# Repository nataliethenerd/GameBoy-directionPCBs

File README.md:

# GameBoy direction PCBs
Direction PCBs for the Game Boy line. These are common ground PCBs that can be used to create mods inside the various Game Boy Shells.

Open source, do whatever you want to do with these! But dont use it to make a submersible controller...

### Navigating this repo
Each folder includes the gerber files, and also all the KiCad files for the boards.

- *.pretty* folders contain the footprints that are used on the board.
- *.zip* files are the gerbers you send the the PCB manufacturer. Order at 1mm ENIG.

#### Game Boy DMG

| Front | Back |
|-------------| -----|
|  |  |

#### Game Boy Pocket

| Front | Back |
|-------------| -----|
|  |  |

#### Game Boy Color

| Front | Back |
|-------------| -----|
|  |  |

## Follow me

If you are into Game Boy modding or retro gaming, please consider using code "NatalieTheNerd" at:

• [Retro Modding](http://RetroModding.com) 

• [Retro Game Repair Shop](http://RetroGameRepairShop.com) 

• [Extreme Rate](http://ExtremeRate.com)

**My socials**

• [Twitter](https://twitter.com/natalie_thenerd) 

• [Instagram](https://www.instagram.com/natalie.thenerd/) 

• [Modded Gameboy Club](https://moddedgameboy.club/) - a club dedicated to the modification of Game Boys, freely sharing resources

## License

Please do not remove my logo, website and name.

The CC BY-SA 4.0 (Creative Commons Attribution-ShareAlike 4.0 International) license allows you to:

1. **Share** - Copy and redistribute the material in any medium or format.
2. **Adapt** - Remix, transform, and build upon the material for any purpose, even commercially.

### Conditions:

- **Attribution** - You must give appropriate credit, provide a link to the license, and indicate if changes were made. You may do so in any reasonable manner, but not in any way that suggests the licensor endorses you or your use.
- **ShareAlike** - If you remix, transform, or build upon the material, you must distribute your contributions under the same license as the original.

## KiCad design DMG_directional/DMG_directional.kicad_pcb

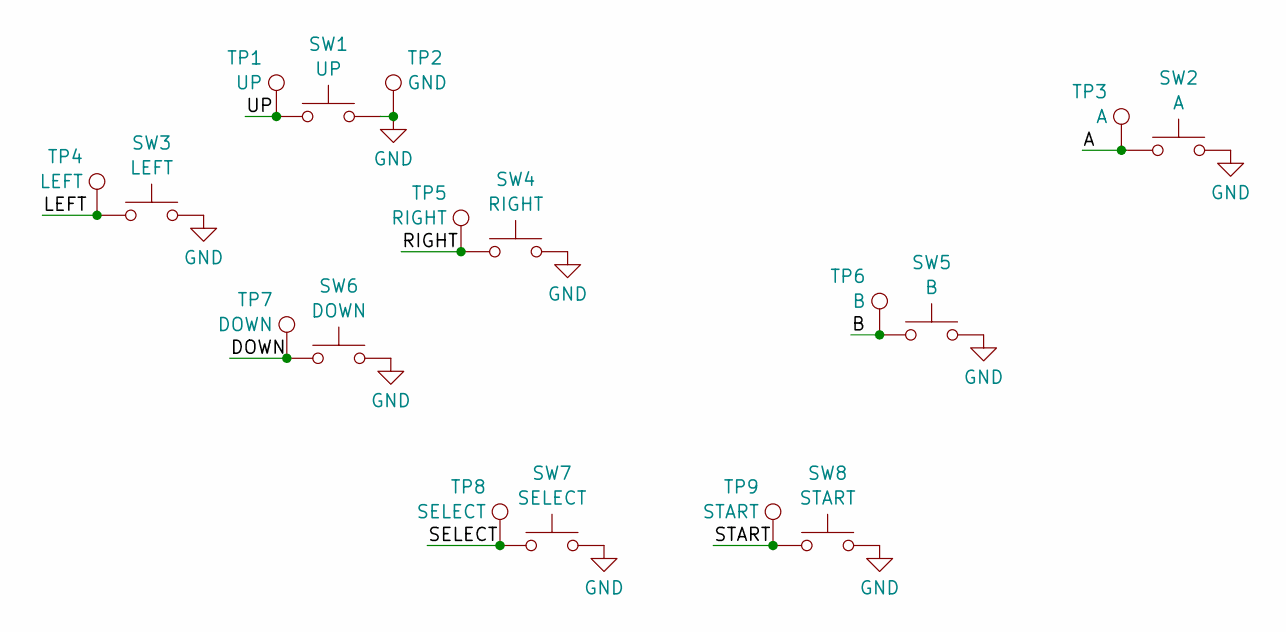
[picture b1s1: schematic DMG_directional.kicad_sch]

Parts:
SW1: UP; Dpad_DMG
SW2: A; AB_DMG
SW3: LEFT; Dpad_DMG
SW4: RIGHT; Dpad_DMG
SW5: B; AB_DMG
SW6: DOWN; Dpad_DMG
SW7: SELECT; Select_DMG
SW8: START; Start_DMG
TP1: UP; TestPoint_THTPad_D1.5mm_Drill0.7mm
TP2: GND; TestPoint_THTPad_D1.5mm_Drill0.7mm
TP3: A; TestPoint_THTPad_D1.5mm_Drill0.7mm
TP4: LEFT; TestPoint_THTPad_D1.5mm_Drill0.7mm
TP5: RIGHT; TestPoint_THTPad_D1.5mm_Drill0.7mm
TP6: B; TestPoint_THTPad_D1.5mm_Drill0.7mm
TP7: DOWN; TestPoint_THTPad_D1.5mm_Drill0.7mm
TP8: SELECT; TestPoint_THTPad_D1.5mm_Drill0.7mm
TP9: START; TestPoint_THTPad_D1.5mm_Drill0.7mm

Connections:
/A: SW2.2, TP3.1
/B: SW5.2, TP6.1
/DOWN: SW6.2, TP7.1
/LEFT: SW3.1, TP4.1
/RIGHT: SW4.2, TP5.1
/SELECT: SW7.1, TP8.1
/START: SW8.1, TP9.1
/UP: SW1.1, TP1.1
GND: SW1.2, SW2.1, SW3.2, SW4.1, SW5.1, SW6.1, SW7.2, SW8.2, TP2.1

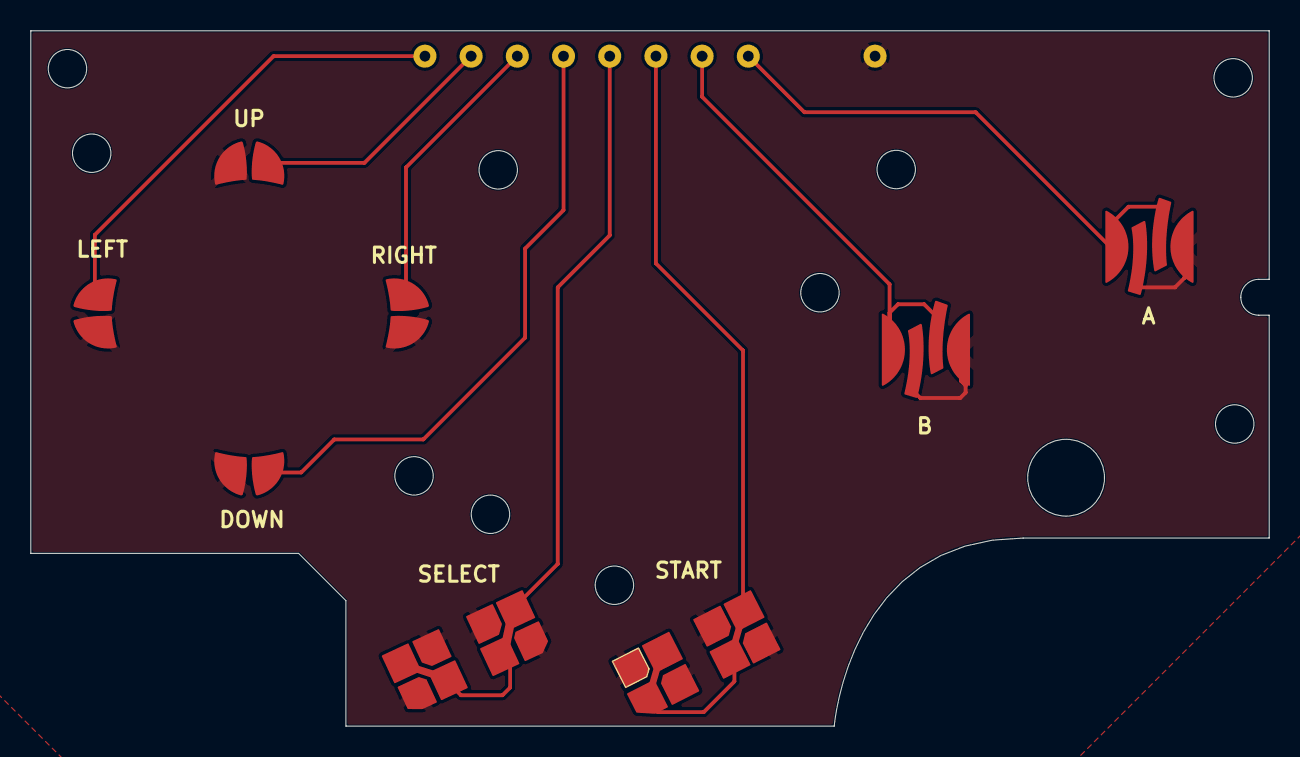
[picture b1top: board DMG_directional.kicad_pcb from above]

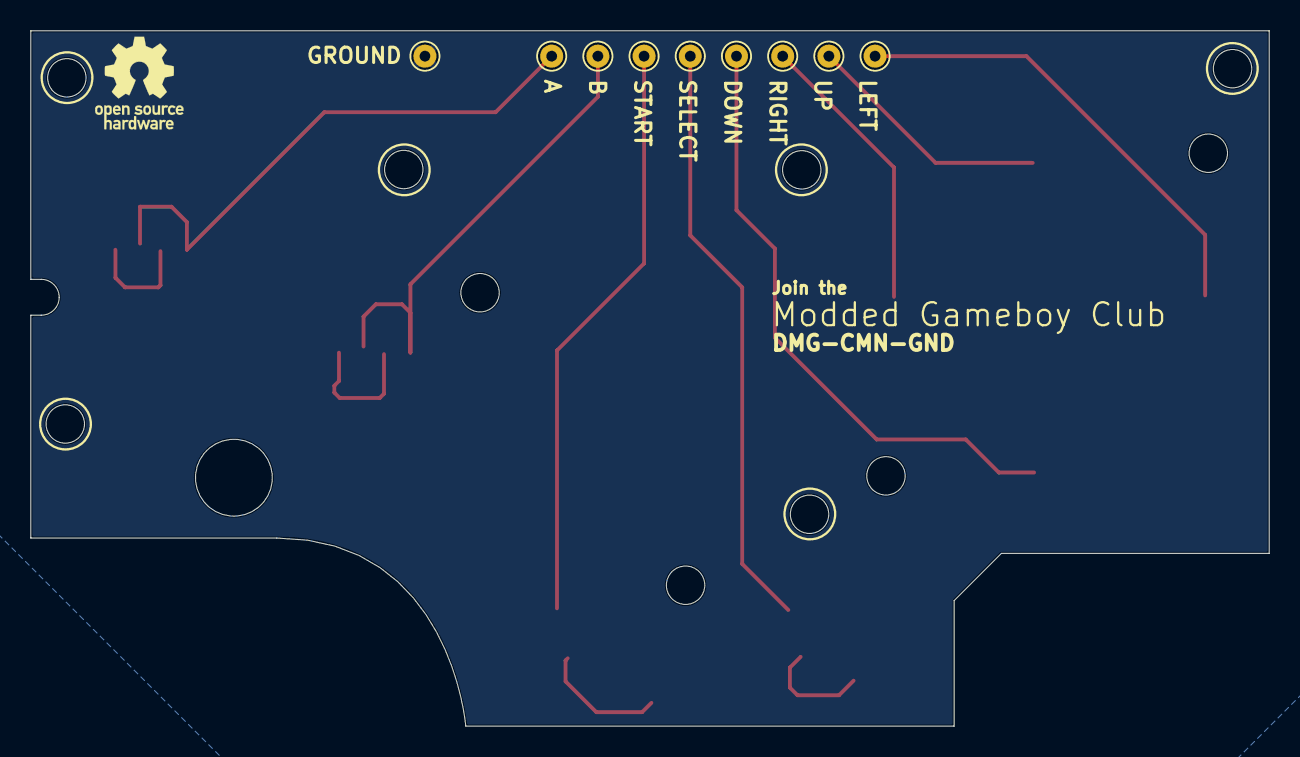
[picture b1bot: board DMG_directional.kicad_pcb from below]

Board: 2 copper layers, 80.6 x 45.3 mm, 17 parts (9 on the bottom side), 9 nets.

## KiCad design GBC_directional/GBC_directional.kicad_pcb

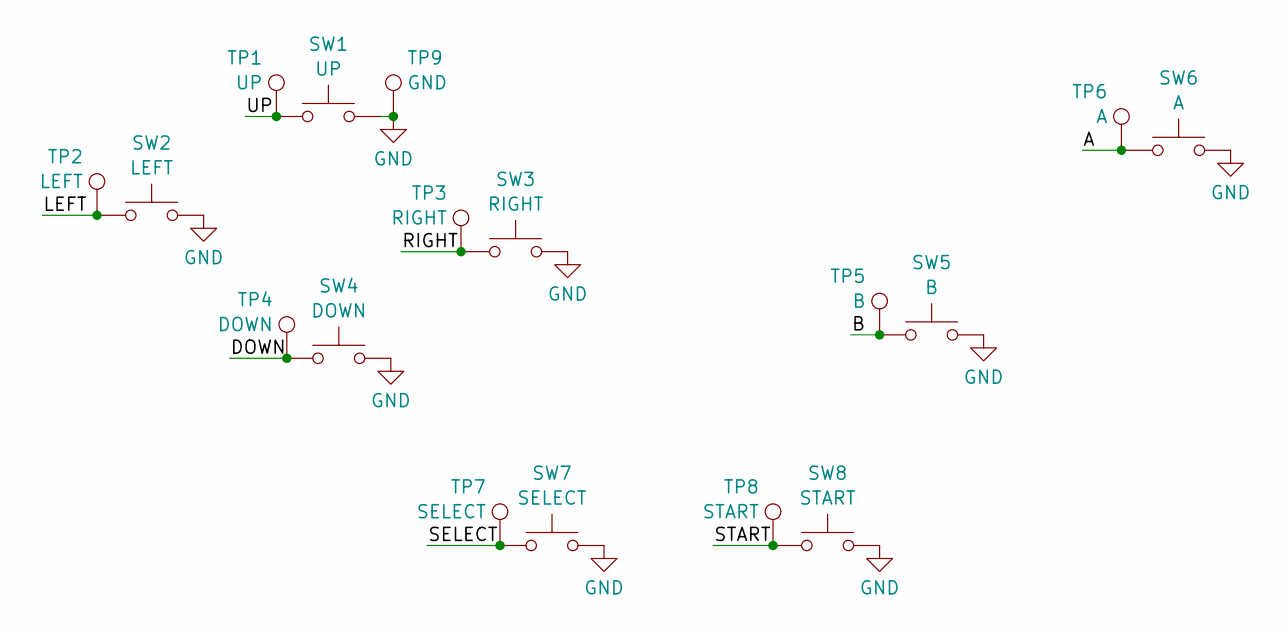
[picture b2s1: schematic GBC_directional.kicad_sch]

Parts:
SW1: UP; Dpad CGB
SW2: LEFT; Dpad CGB
SW3: RIGHT; Dpad CGB
SW4: DOWN; Dpad CGB
SW5: B; AB CGB
SW6: A; AB CGB
SW7: SELECT; Select CGB
SW8: START; Start CGB
TP1: UP; TestPoint_THTPad_D1.5mm_Drill0.7mm
TP2: LEFT; TestPoint_THTPad_D1.5mm_Drill0.7mm
TP3: RIGHT; TestPoint_THTPad_D1.5mm_Drill0.7mm
TP4: DOWN; TestPoint_THTPad_D1.5mm_Drill0.7mm
TP5: B; TestPoint_THTPad_D1.5mm_Drill0.7mm
TP6: A; TestPoint_THTPad_D1.5mm_Drill0.7mm
TP7: SELECT; TestPoint_THTPad_D1.5mm_Drill0.7mm
TP8: START; TestPoint_THTPad_D1.5mm_Drill0.7mm
TP9: GND; TestPoint_THTPad_D1.5mm_Drill0.7mm

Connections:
/A: SW6.2, TP6.1
/B: SW5.2, TP5.1
/DOWN: SW4.2, TP4.1
/LEFT: SW2.1, TP2.1
/RIGHT: SW3.2, TP3.1
/SELECT: SW7.2, TP7.1
/START: SW8.2, TP8.1
/UP: SW1.1, TP1.1
GND: SW1.2, SW2.2, SW3.1, SW4.1, SW5.1, SW6.1, SW7.1, SW8.1, TP9.1

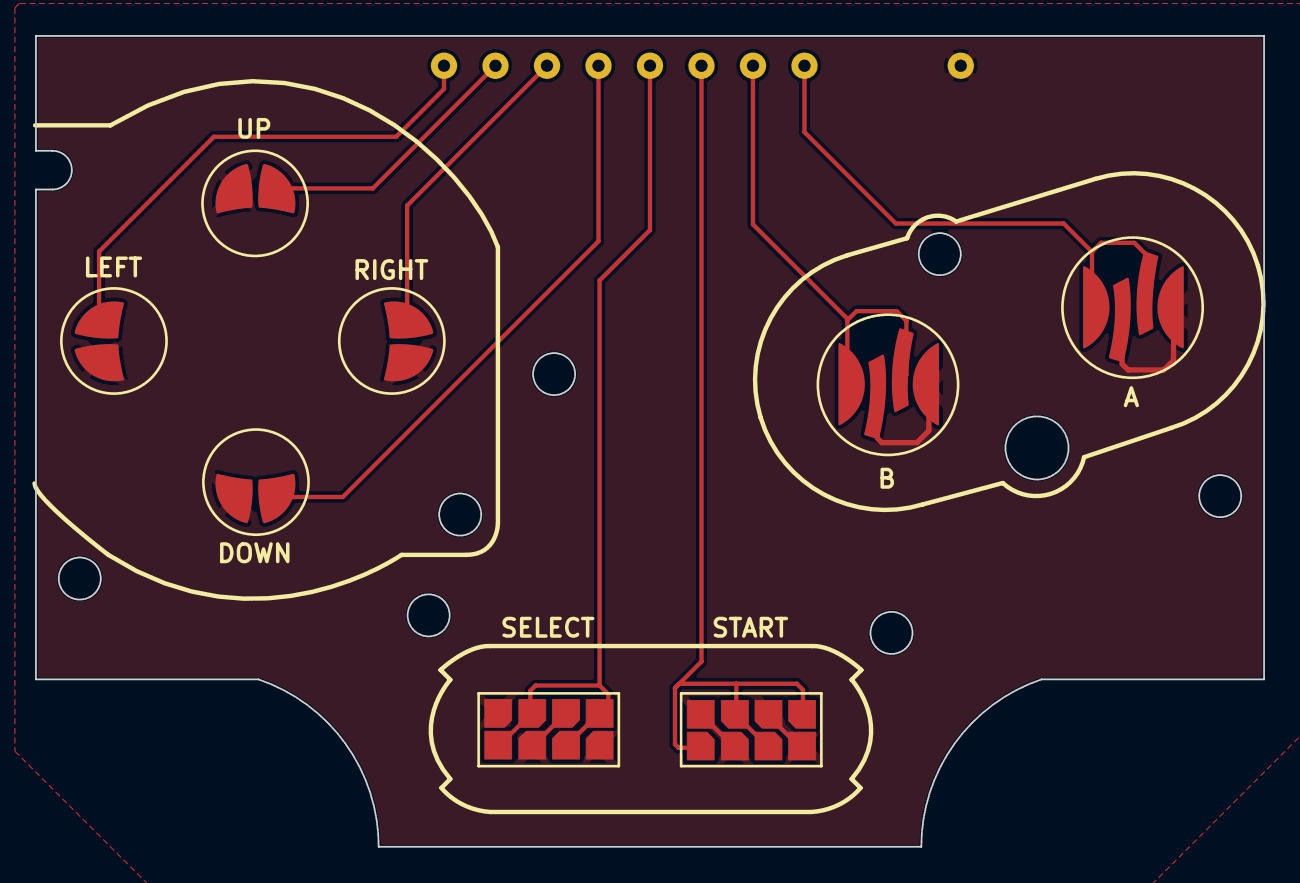
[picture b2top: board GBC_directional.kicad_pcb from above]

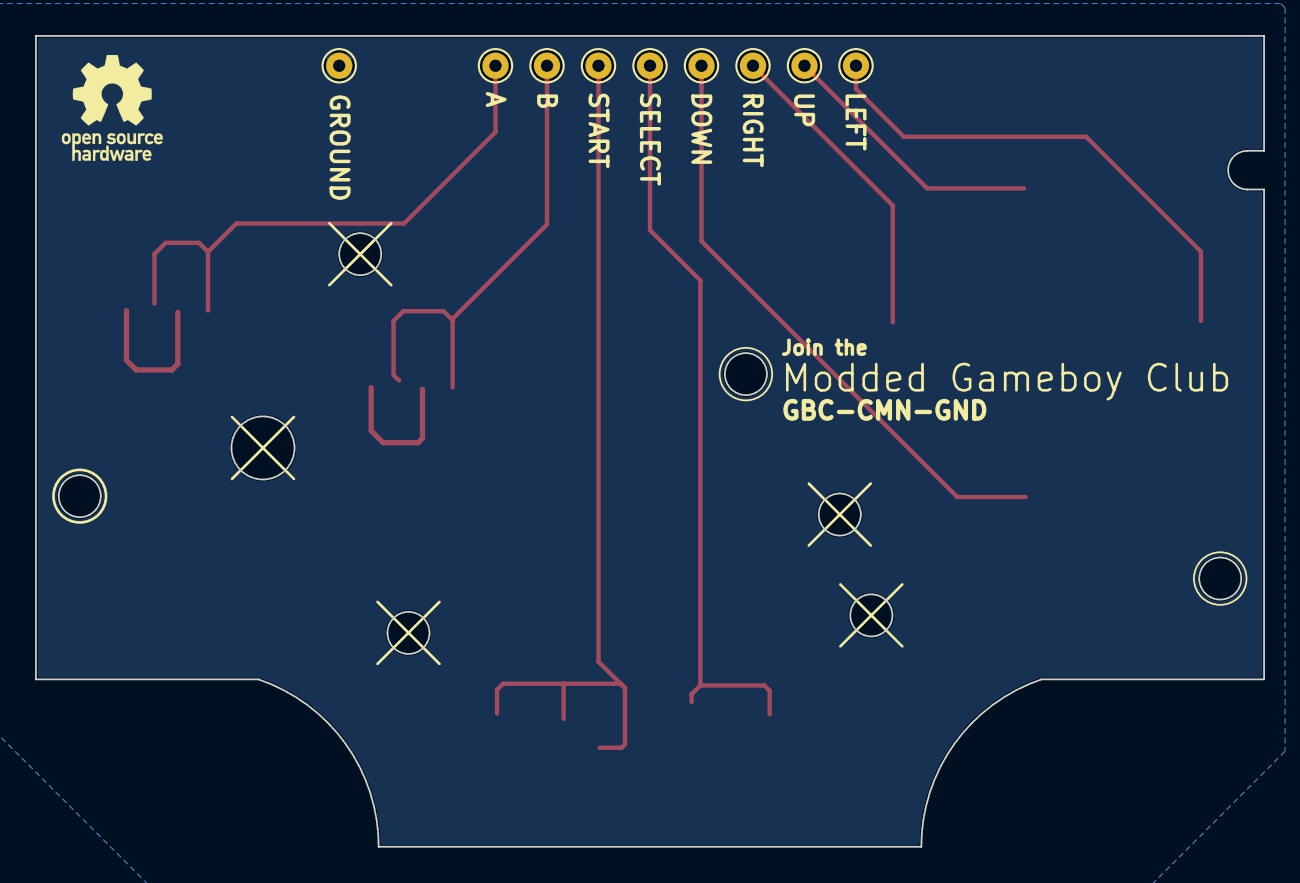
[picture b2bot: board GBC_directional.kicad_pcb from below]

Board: 2 copper layers, 70.0 x 46.2 mm, 17 parts (9 on the bottom side), 9 nets.

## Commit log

2025-07-11 gbc added
2025-07-12 pocket
2025-07-12 added dmg
